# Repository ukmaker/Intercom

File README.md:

What Is it?
==================
This project implements a wireless intercom system using the RFM12B radio
module and the Atmega 328P microcontroller running the Arduino environment.

Why Does it Exist?
===================
I wanted a wireless intercom so I could stop shouting up the stairs at the kids.

The consensus on the web was that the RFM12B is not suitable for speech: challenge!

What Does It Do?
===================
Implements a five-station intercom with the following features:

  - Call each station individually (station to station)
  - Call all stations together (broadcast)
  - LED indicates which station is calling
  - Uses low power sleep modes when not in use giving up to 3 months life on a PP3 battery
  
How Does It Do It?
===================

  - Atmega 328P running at 16MHz
  - Microphone AGC circuit
  - 8-bit audio sampled at 8kHz
  - RFM12B running at 115kBaud
  - Range in excess of 20m (depends on length of aerial)

What's Wrong With It?
======================
The circuit design is fine and works well, but:

  - Battery life could be better - the RFM12B is a bit of a hog. Use a 9V wall-wart if you're bothered.
  - The PCB layout sucks. Sorry. If I had time I'd do it again using SMD parts, and I'd probably 
  use a more modern, lower power replacement for the RFM12B.
  
Dependencies
=================
Relies on my RFM12B library - a non-blocking, event-driven implementation. Get it here:

https://github.com/ukmaker/RFM12BE

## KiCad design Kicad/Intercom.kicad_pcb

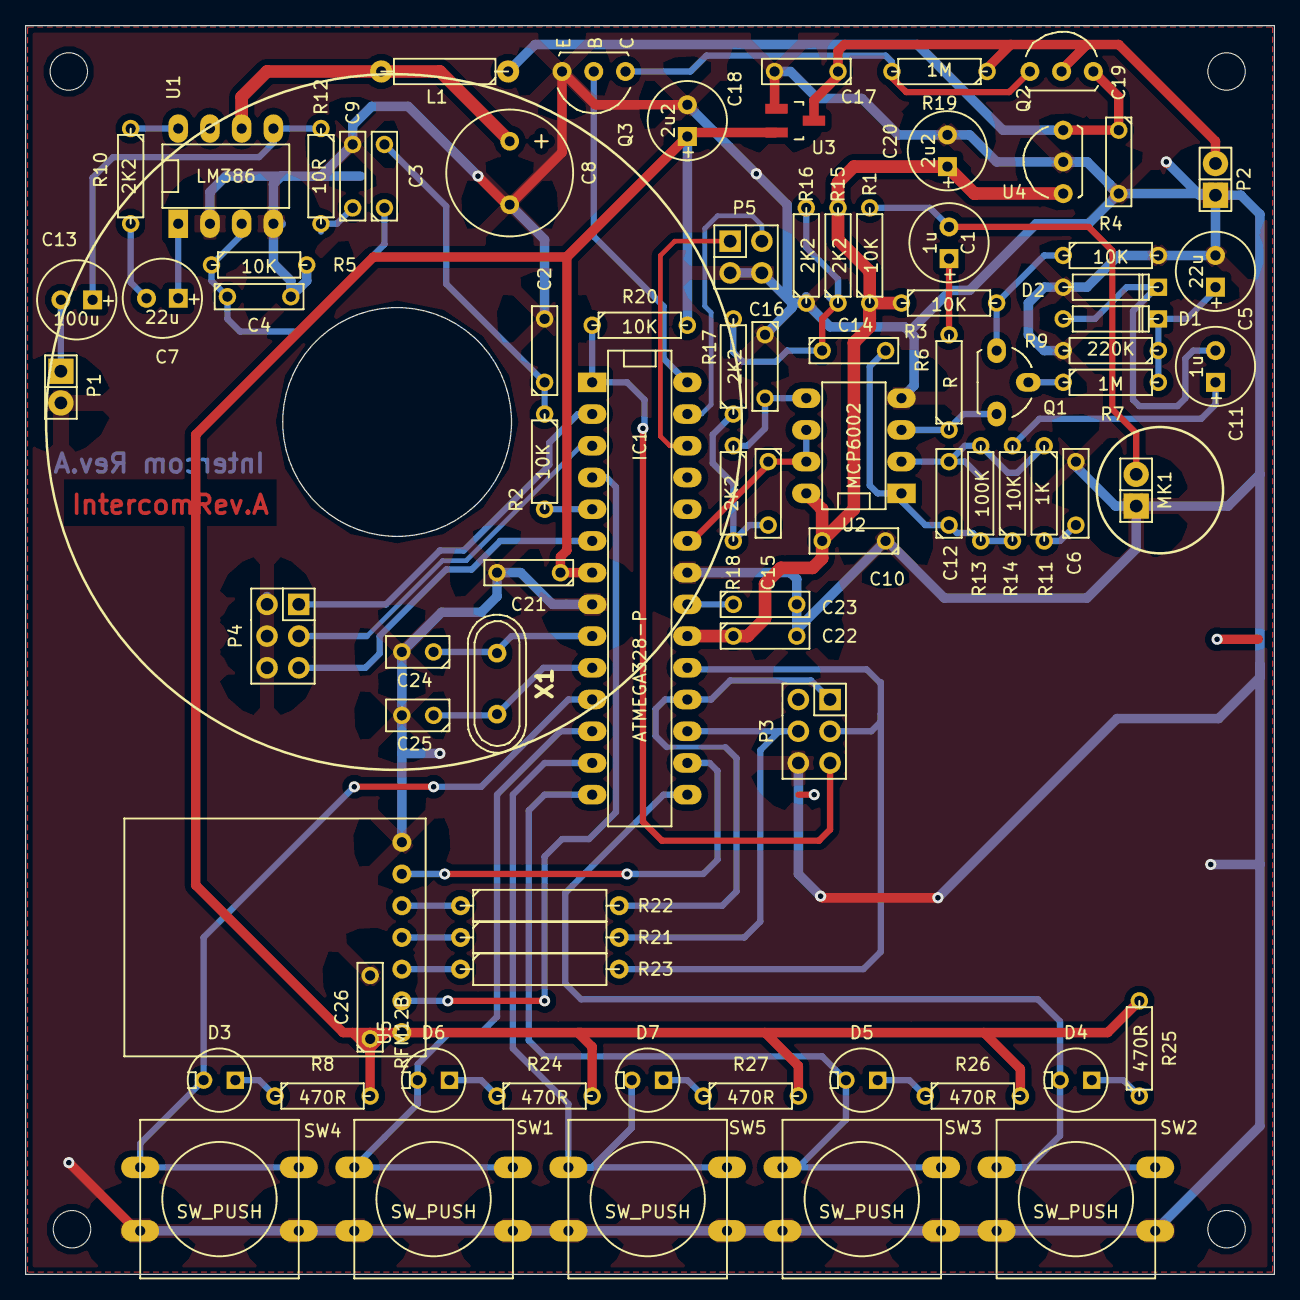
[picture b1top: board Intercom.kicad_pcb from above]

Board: 2 copper layers, 100.0 x 100.0 mm, 86 parts (0 on the bottom side), 59 nets.

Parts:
C1, C11: 1u; C1V7
C2: 200n; C2
C3, C6, C10, C19, C21, C22, C23, C26: 100n; C2
C4: 470p; C2
C5, C7: 22u; C1V7
C8: 1200u; Elko_vert_20x10mm_RM5
C9, C15: 47n; C2
C12: 2n2; C2
C13: 100u; C1V7
C14: 220n; C2
C16: 22n; C2
C17: 1u; C2
C18, C20: 2u2; C1V7
C24, C25: 22p; C1
D1, D2: BAT43; D3
D3, D4, D5, D6, D7: LED; LEDV
IC1: ATMEGA328-P; DIP-28__300_ELL
L1: 100u; R4-LARGE_PADS
MK1: MIC9.7MM; Socket_Strip_Straight_1x02
MountingHole_3mm, MountingHole_3mm#2, MountingHole_3mm#3, MountingHole_3mm#4: VAL**; MountingHole_3mm
P1, P2: CONN_2; Socket_Strip_Straight_1x02
P3, P4: CONN_3X2; Socket_Strip_Straight_2x03
P5: CONN_2X2; Socket_Strip_Straight_2x02
Q1: BF244A; TO-92-FET-molded-wide-oval-SGD
Q2: IRFU3505; TO-92-Free-inline-wide
Q3: ZTX313; TO-92-Bipolar-inline-wide-CBE
R1, R2, R3, R4, R5, R14, R20: 10K; R3
R6: R; R3
R7, R19: 1M; R3
R8, R24, R25, R26, R27: 470R; R3
R9: 220K; R3
R10, R15, R16, R17, R18: 2K2; R3
R11: 1K; R3
R12: 10R; R3
R13: 100K; R3
R21, R22, R23: 1K; R5
SW1, SW2, SW3, SW4, SW5: SW_PUSH; SW_PUSH-12mm
U1: LM386; DIP-8__300_ELL
U2: MCP6002; DIP-8__300_ELL
U3: MCP1700T; SOT23_Transistor_Handsoldering_RevB_14Mar2014
U4: LE33CZ; TO-92-Free-inline-wide
U5: RFM12B
X1: 16MHz; Crystal_HC49-U_Vertical

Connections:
+3.3V: C18.1, C21.1, C26.1, IC1.7, R8.2, R20.2, R24.2, R25.2, R26.2, R27.2, U3.VO, U5.7
+9V: C19.1, L1.1, Q2.S, U4.VI
/Control/MIC: C15.1, IC1.23, U2.6, U2.7
/Control/POWERON: IC1.28, Q3.2
/Control/SPKR: IC1.5, R2.2
C1: D3.2, IC1.11, SW4.1
C2: D6.2, IC1.12, SW1.1
C3: D7.2, IC1.13, SW5.1
C4: D5.2, IC1.14, SW3.1
C5: D4.2, IC1.15, SW2.1
CH0: IC1.26, P5.1
CH1: IC1.27, P5.3
GND: C2.2, C4.2, C5.2, C6.2, C8.2, C9.2, C10.1, C16.1, C17.2, C18.2, C19.2, C20.2, C21.2, C22.2, C23.2, C24.2, C25.2, C26.2, D2.1, IC1.8, IC1.22, MK1.1, P1.2, P2.1, P3.6, P4.2, P4.4, P4.6, P5.2, P5.4, Q3.1, R4.2, R5.2, R9.2, R16.1, SW1.2, SW2.2, SW3.2, SW4.2, SW5.2, U1.2, U1.4, U2.4, U3.GND, U4.GND, U5.1
unnamed: C1.1, R6.2
unnamed: C1.2, MK1.2, R1.2
unnamed: C2.1, C3.2, R2.1
unnamed: C3.1, C4.1, R5.1, U1.3
unnamed: C5.1, D1.2, R7.2, R9.1
unnamed: C6.1, R11.2
unnamed: C7.1, U1.1
unnamed: C7.2, R10.2
unnamed: C8.1, L1.2, U1.6
unnamed: C9.1, R12.2
unnamed: C11.1, R14.2
unnamed: C11.2, D1.1, D2.2
unnamed: C12.1, C14.2, R13.1, R14.1, U2.1
unnamed: C12.2, R11.1, R13.2, U2.2
unnamed: C13.1, R12.1, U1.5
unnamed: C13.2, P1.1
unnamed: C14.1, R15.1, R16.2, R17.2
unnamed: C15.2, R17.1, R18.2
unnamed: C16.2, R18.1, U2.5
unnamed: C17.1, P2.2, Q2.D, R19.1, U3.VI
unnamed: C23.1, IC1.21
unnamed: D3.1, R8.1
unnamed: D4.1, R25.1
unnamed: D5.1, R26.1
unnamed: D6.1, R24.1
unnamed: D7.1, R27.1
unnamed: IC1.1, P3.5, R20.1
unnamed: IC1.4, U5.6
unnamed: IC1.16, U5.2
unnamed: IC1.17, P3.4, R21.2
unnamed: IC1.18, P3.1, R22.2
unnamed: IC1.19, P3.3, R23.2
unnamed: Q1.1, R6.1, U2.3
unnamed: Q1.2, R7.1
unnamed: Q1.3, R3.2, R4.1
unnamed: Q2.G, Q3.3, R19.2
unnamed: R10.1, U1.8
unnamed: R21.1, U5.4
unnamed: R22.1, U5.3
unnamed: R23.1, U5.5
ST0: IC1.2, P4.1
ST1: IC1.3, P4.3
ST2: IC1.6, P4.5
VAA: C10.2, C20.1, C22.1, IC1.20, R1.1, R3.1, R15.2, U2.8, U4.VO
X1: C24.1, IC1.9, X1.1
X2: C25.1, IC1.10, X1.2

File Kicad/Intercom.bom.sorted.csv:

R13,100K,,
C10,100n,,
C19,100n,,
C21,100n,,
C22,100n,,
C23,100n,,
C26,100n,,
C3,100n,,
C6,100n,,
C13,100u,,
L1,100u,,
R1,10K,,
R14,10K,,
R20,10K,,
R2,10K,,
R3,10K,,
R4,10K,,
R5,10K,,
R12,10R,,
C8,1200u,,
X1,16MHz,,
R11,1K,,
R21,1K,,
R22,1K,,
R23,1K,,
R19,1M,,
R7,1M,,
C11,1u,,
C1,1u,,
C17,1u,,
C2,200n,,
R9,220K,,
C14,220n,,
C16,22n,,
C24,22p,,
C25,22p,,
C5,22u,,
C7,22u,,
R10,2K2,,
R15,2K2,,
R16,2K2,,
R17,2K2,,
R18,2K2,,
C12,2n2,,
C18,2u2,,
C20,2u2,,
C4,470p,,
R24,470R,,
R25,470R,,
R26,470R,,
R27,470R,,
R8,470R,,
C15,47n,,
C9,47n,,
IC1,ATMEGA328-P,DIL28,
D1,BAT43,,
D2,BAT43,,
Q1,BF244A,TO92,
P1,CONN_2,,
P2,CONN_2,,
P5,CONN_2X2,,
P3,CONN_3X2,,
P4,CONN_3X2,,
Q2,IRFU3505,,
U4,LE33CZ,,
D3,LED,,
D4,LED,,
D5,LED,,
D6,LED,,
D7,LED,,
U1,LM386,,
U3,MCP1700T,,
U2,MCP6002,,
MK1,MIC9.7MM,,
R6,R,,
U5,RFM12B,,
SW1,SW_PUSH,,
SW2,SW_PUSH,,
SW3,SW_PUSH,,
SW4,SW_PUSH,,
SW5,SW_PUSH,,
Reference, Value, Footprint, Datasheet
Q3,ZTX313,,

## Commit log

2015-02-21 Initial import
2015-03-14 Added OpenSCAD WIP
2015-06-04 Added README and pictures
